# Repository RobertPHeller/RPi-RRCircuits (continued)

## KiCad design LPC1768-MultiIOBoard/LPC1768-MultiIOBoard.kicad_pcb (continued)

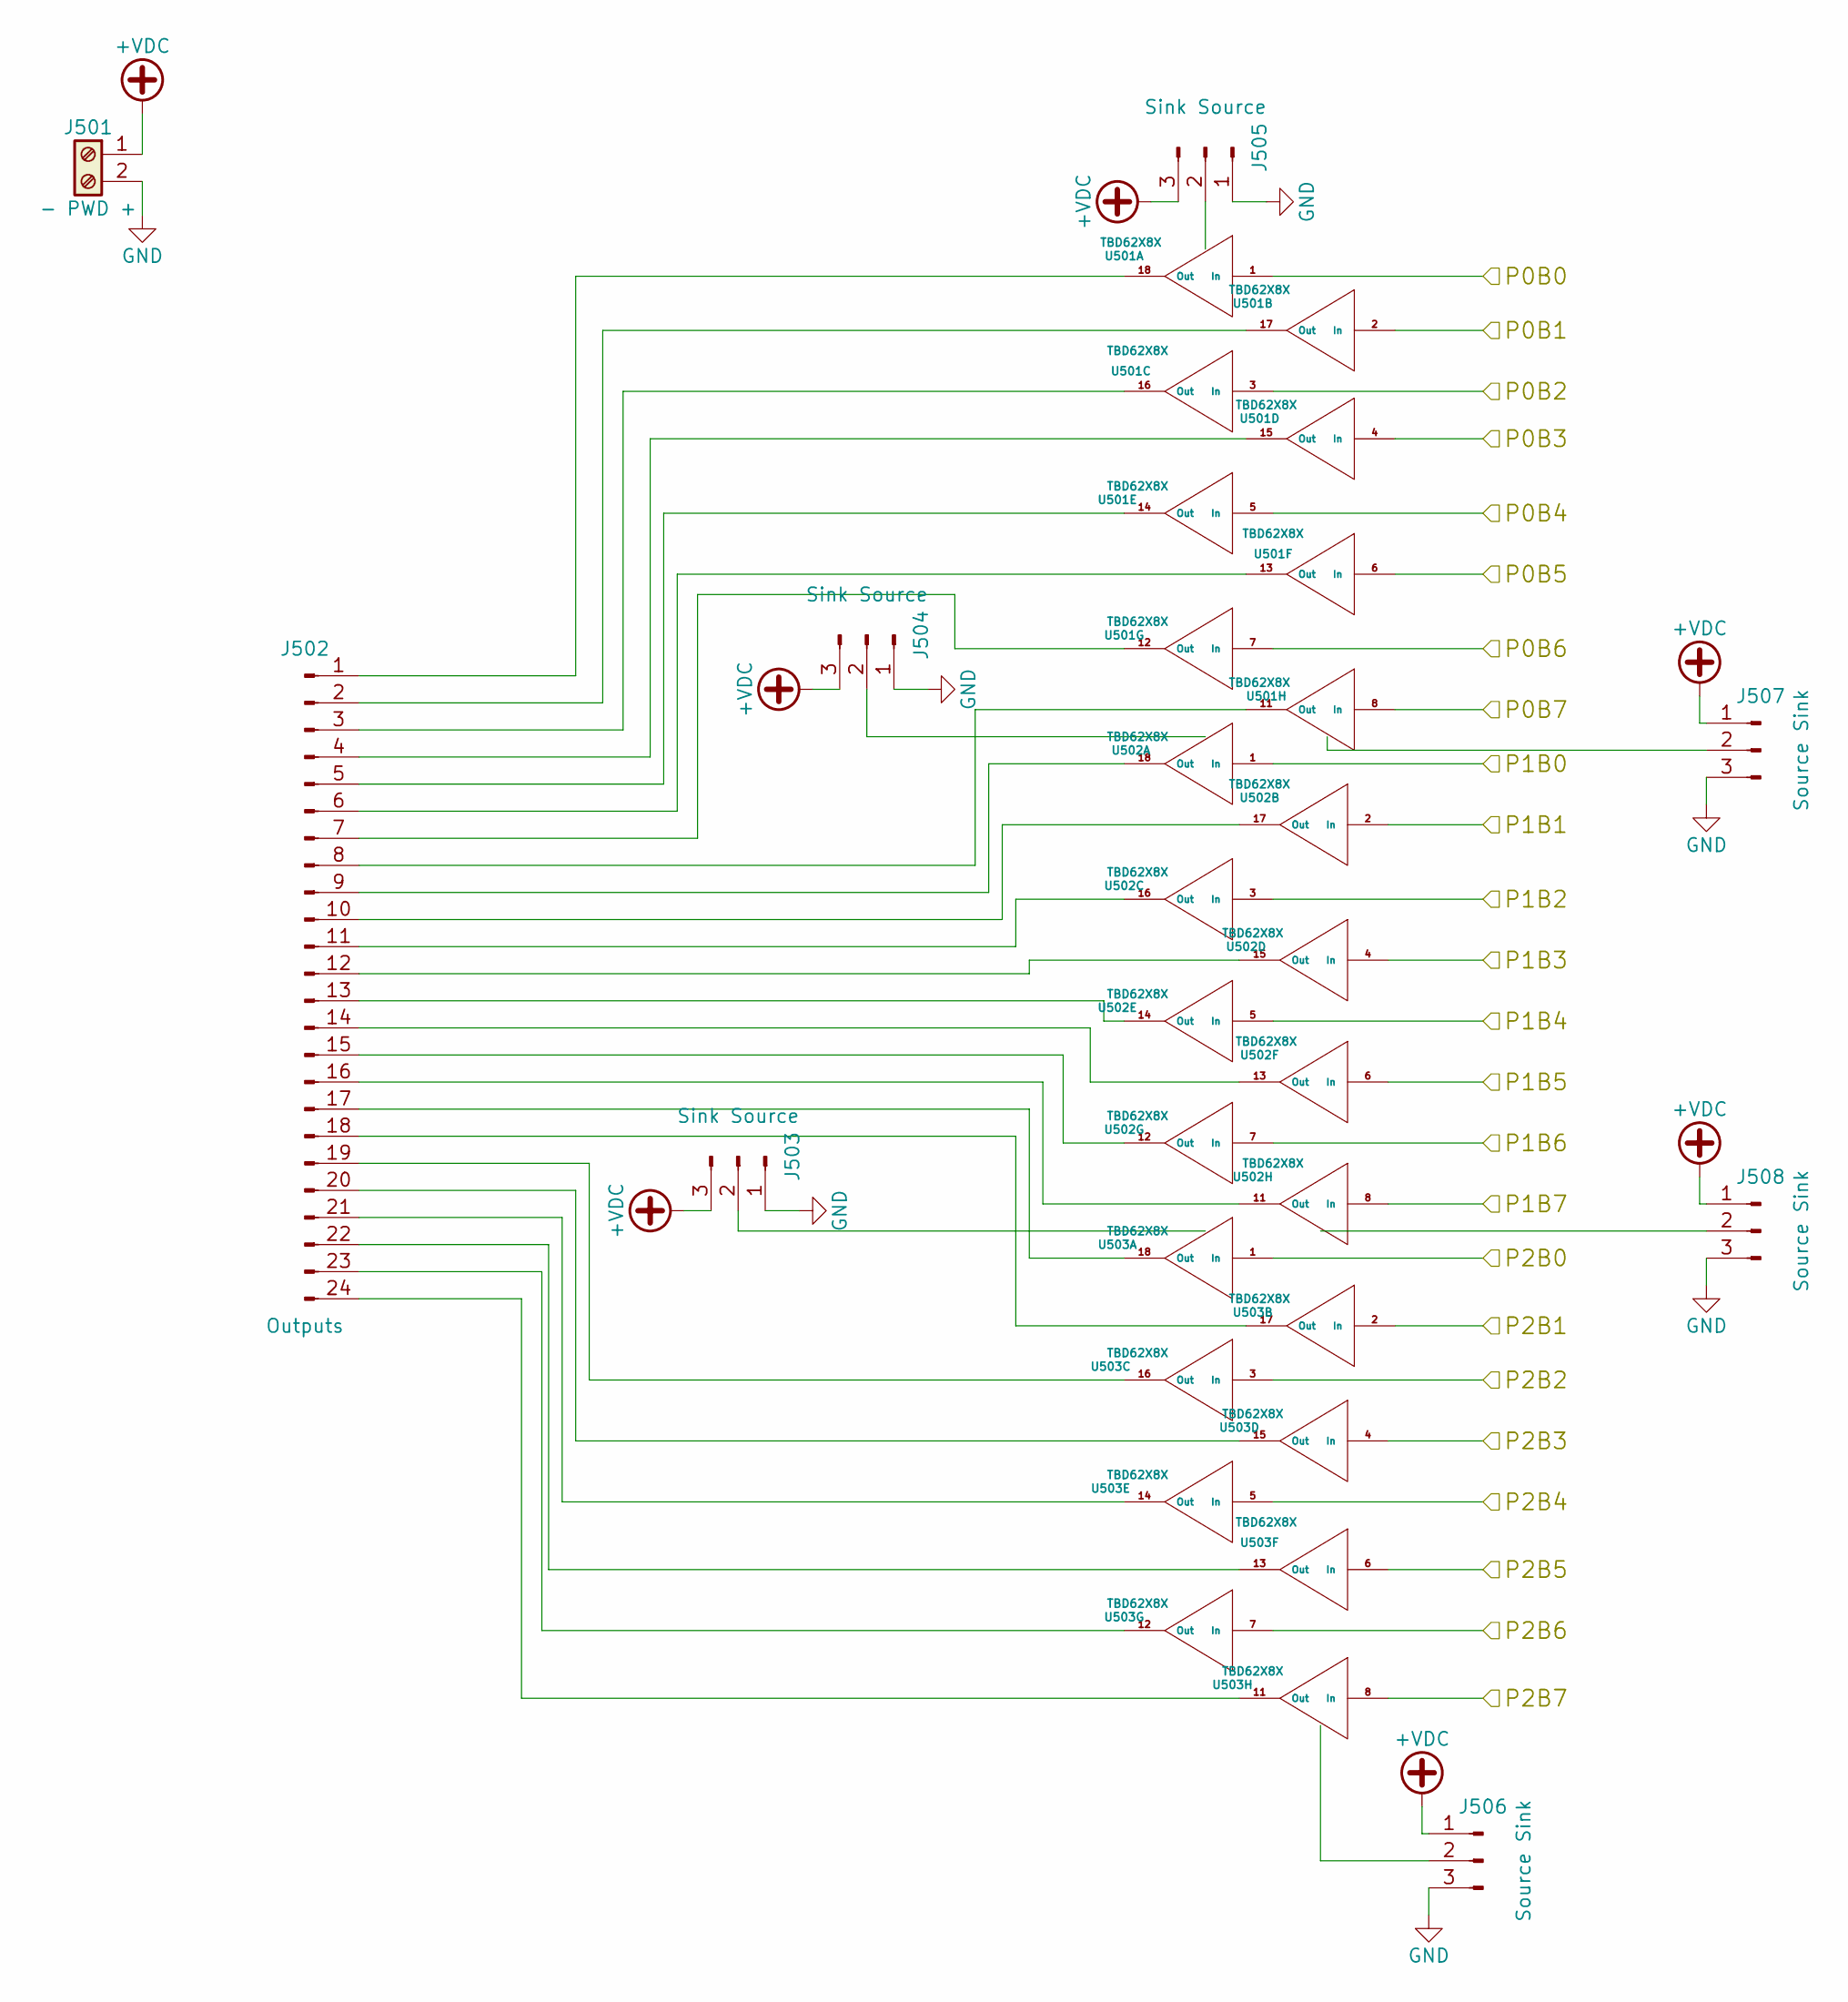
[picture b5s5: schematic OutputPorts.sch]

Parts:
J501: - PWD +; TerminalBlock_Pheonix_MPT-2.54mm_2pol
J502: Outputs; Molex_KK_396_01x24_3.96mm_RightAngle; Mouser Part Number 538-26-48-1242
J503, J504, J505: Sink Source; Pin_Header_Straight_1x03_Pitch2.54mm
J506, J507, J508: Source Sink; Pin_Header_Straight_1x03_Pitch2.54mm
U501, U502, U503: TBD62X8X; DIP-18_W7.62mm; Mouser Part Number 571-1-2199298-5

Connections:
+VDC: J501.1, J503.3, J504.3, J505.3, J506.1, J507.1, J508.1
/Micro Processor Unit/C1P0B0: U501.1 (In); also elsewhere on the board
/Micro Processor Unit/C1P0B1: U501.2 (In); also elsewhere on the board
/Micro Processor Unit/C1P0B2: U501.3 (In); also elsewhere on the board
/Micro Processor Unit/C1P0B3: U501.4 (In); also elsewhere on the board
/Micro Processor Unit/C1P0B4: U501.5 (In); also elsewhere on the board
/Micro Processor Unit/C1P0B5: U501.6 (In); also elsewhere on the board
/Micro Processor Unit/C1P0B6: U501.7 (In); also elsewhere on the board
/Micro Processor Unit/C1P0B7: U501.8 (In); also elsewhere on the board
/Micro Processor Unit/C1P1B0: U502.1 (In); also elsewhere on the board
/Micro Processor Unit/C1P1B1: U502.2 (In); also elsewhere on the board
/Micro Processor Unit/C1P1B2: U502.3 (In); also elsewhere on the board
/Micro Processor Unit/C1P1B3: U502.4 (In); also elsewhere on the board
/Micro Processor Unit/C1P1B4: U502.5 (In); also elsewhere on the board
/Micro Processor Unit/C1P1B5: U502.6 (In); also elsewhere on the board
/Micro Processor Unit/C1P1B6: U502.7 (In); also elsewhere on the board
/Micro Processor Unit/C1P1B7: U502.8 (In); also elsewhere on the board
/Micro Processor Unit/C1P2B0: U503.1 (In); also elsewhere on the board
/Micro Processor Unit/C1P2B1: U503.2 (In); also elsewhere on the board
/Micro Processor Unit/C1P2B2: U503.3 (In); also elsewhere on the board
/Micro Processor Unit/C1P2B3: U503.4 (In); also elsewhere on the board
/Micro Processor Unit/C1P2B4: U503.5 (In); also elsewhere on the board
/Micro Processor Unit/C1P2B5: U503.6 (In); also elsewhere on the board
/Micro Processor Unit/C1P2B6: U503.7 (In); also elsewhere on the board
/Micro Processor Unit/C1P2B7: U503.8 (In); also elsewhere on the board
GND: J501.2, J503.1, J504.1, J505.1, J506.3, J507.3, J508.3; also elsewhere on the board
unnamed: J502.1, U501.18 (Out)
unnamed: J502.2, U501.17 (Out)
unnamed: J502.3, U501.16 (Out)
unnamed: J502.4, U501.15 (Out)
unnamed: J502.5, U501.14 (Out)
unnamed: J502.6, U501.13 (Out)
unnamed: J502.7, U501.12 (Out)
unnamed: J502.8, U501.11 (Out)
unnamed: J502.9, U502.18 (Out)
unnamed: J502.10, U502.17 (Out)
unnamed: J502.11, U502.16 (Out)
unnamed: J502.12, U502.15 (Out)
unnamed: J502.13, U502.14 (Out)
unnamed: J502.14, U502.13 (Out)
unnamed: J502.15, U502.12 (Out)
unnamed: J502.16, U502.11 (Out)
unnamed: J502.17, U503.18 (Out)
unnamed: J502.18, U503.17 (Out)
unnamed: J502.19, U503.16 (Out)
unnamed: J502.20, U503.15 (Out)
unnamed: J502.21, U503.14 (Out)
unnamed: J502.22, U503.13 (Out)
unnamed: J502.23, U503.12 (Out)
unnamed: J502.24, U503.11 (Out)
unnamed: J503.2, U503.10 (OC)
unnamed: J504.2, U502.10 (OC)
unnamed: J505.2, U501.10 (OC)
unnamed: J506.2, U503.9 (IC)
unnamed: J507.2, U501.9 (IC)
unnamed: J508.2, U502.9 (IC)

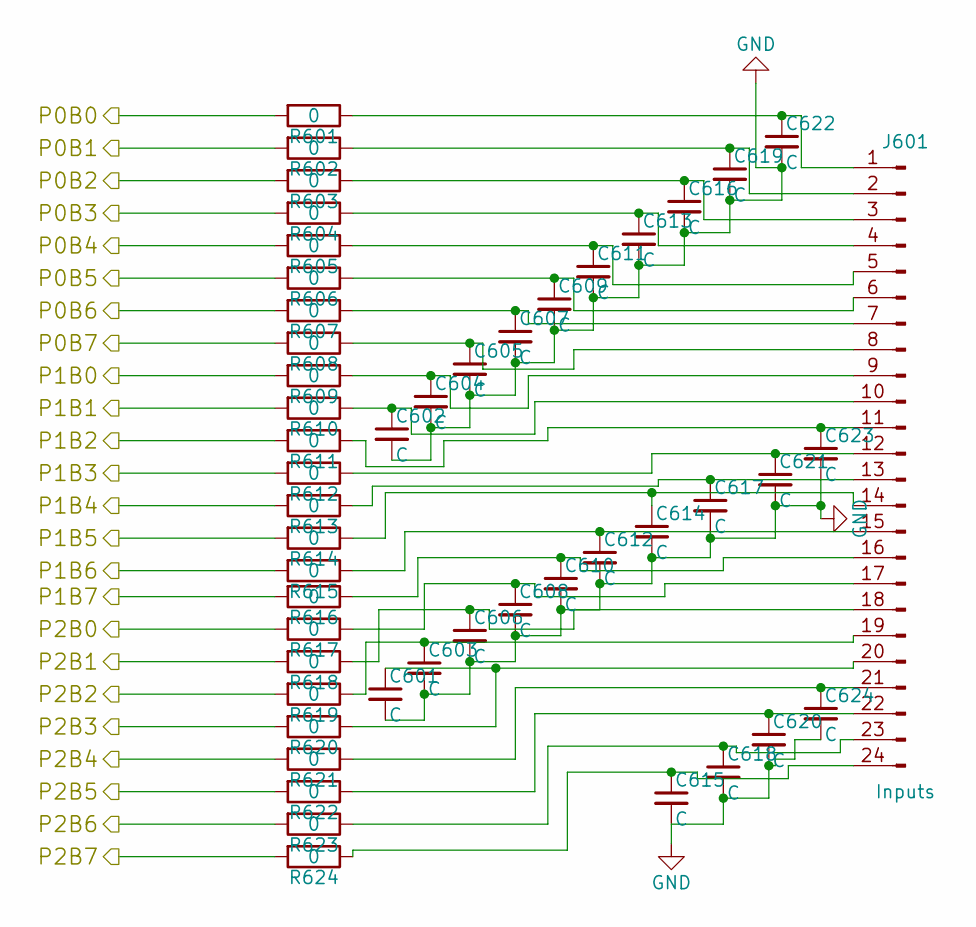
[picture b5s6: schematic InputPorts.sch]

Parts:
C601, C602, C603, C604, C605, C606, C607, C608, C609, C610, C611, C612, C613, C614, C615, C616, C617, C618, C619, C620, C621, C622, C623, C624: C; C_Disc_D3.8mm_W2.6mm_P2.50mm
J601: Inputs; Molex_KK_396_01x24_3.96mm_RightAngle; Mouser Part Number 538-26-48-1242
R601, R602, R603, R604, R605, R606, R607, R608, R609, R610, R611, R612, R613, R614, R615, R616, R617, R618, R619, R620, R621, R622, R623, R624: 0; R_Axial_DIN0207_L6.3mm_D2.5mm_P10.16mm_Horizontal_WJumper

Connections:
/Micro Processor Unit/C0P0B0: R601.2; also elsewhere on the board
/Micro Processor Unit/C0P0B1: R602.2; also elsewhere on the board
/Micro Processor Unit/C0P0B2: R603.2; also elsewhere on the board
/Micro Processor Unit/C0P0B3: R604.2; also elsewhere on the board
/Micro Processor Unit/C0P0B4: R605.2; also elsewhere on the board
/Micro Processor Unit/C0P0B5: R606.2; also elsewhere on the board
/Micro Processor Unit/C0P0B6: R607.2; also elsewhere on the board
/Micro Processor Unit/C0P0B7: R608.2; also elsewhere on the board
/Micro Processor Unit/C0P1B0: R609.2; also elsewhere on the board
/Micro Processor Unit/C0P1B1: R610.2; also elsewhere on the board
/Micro Processor Unit/C0P1B2: R611.2; also elsewhere on the board
/Micro Processor Unit/C0P1B3: R612.2; also elsewhere on the board
/Micro Processor Unit/C0P1B4: R613.2; also elsewhere on the board
/Micro Processor Unit/C0P1B5: R614.2; also elsewhere on the board
/Micro Processor Unit/C0P1B6: R615.2; also elsewhere on the board
/Micro Processor Unit/C0P1B7: R616.2; also elsewhere on the board
/Micro Processor Unit/C0P2B0: R617.2; also elsewhere on the board
/Micro Processor Unit/C0P2B1: R618.2; also elsewhere on the board
/Micro Processor Unit/C0P2B2: R619.2; also elsewhere on the board
/Micro Processor Unit/C0P2B3: R620.2; also elsewhere on the board
/Micro Processor Unit/C0P2B4: R621.2; also elsewhere on the board
/Micro Processor Unit/C0P2B5: R622.2; also elsewhere on the board
/Micro Processor Unit/C0P2B6: R623.2; also elsewhere on the board
/Micro Processor Unit/C0P2B7: R624.2; also elsewhere on the board
GND: C601.2, C602.2, C603.2, C604.2, C605.2, C606.2, C607.2, C608.2, C609.2, C610.2, C611.2, C612.2, C613.2, C614.2, C615.2, C616.2, C617.2, C618.2, C619.2, C620.2, C621.2, C622.2, C623.2, C624.2; also elsewhere on the board
unnamed: C601.1, J601.20, R620.1
unnamed: C602.1, J601.10, R610.1
unnamed: C603.1, J601.19, R619.1
unnamed: C604.1, J601.9, R609.1
unnamed: C605.1, J601.8, R608.1
unnamed: C606.1, J601.18, R618.1
unnamed: C607.1, J601.7, R607.1
unnamed: C608.1, J601.17, R617.1
unnamed: C609.1, J601.6, R606.1
unnamed: C610.1, J601.16, R616.1
unnamed: C611.1, J601.5, R605.1
unnamed: C612.1, J601.15, R615.1
unnamed: C613.1, J601.4, R604.1
unnamed: C614.1, J601.14, R614.1
unnamed: C615.1, J601.24, R624.1
unnamed: C616.1, J601.3, R603.1
unnamed: C617.1, J601.13, R613.1
unnamed: C618.1, J601.23, R623.1
unnamed: C619.1, J601.2, R602.1
unnamed: C620.1, J601.22, R622.1
unnamed: C621.1, J601.12, R612.1
unnamed: C622.1, J601.1, R601.1
unnamed: C623.1, J601.11, R611.1
unnamed: C624.1, J601.21, R621.1

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
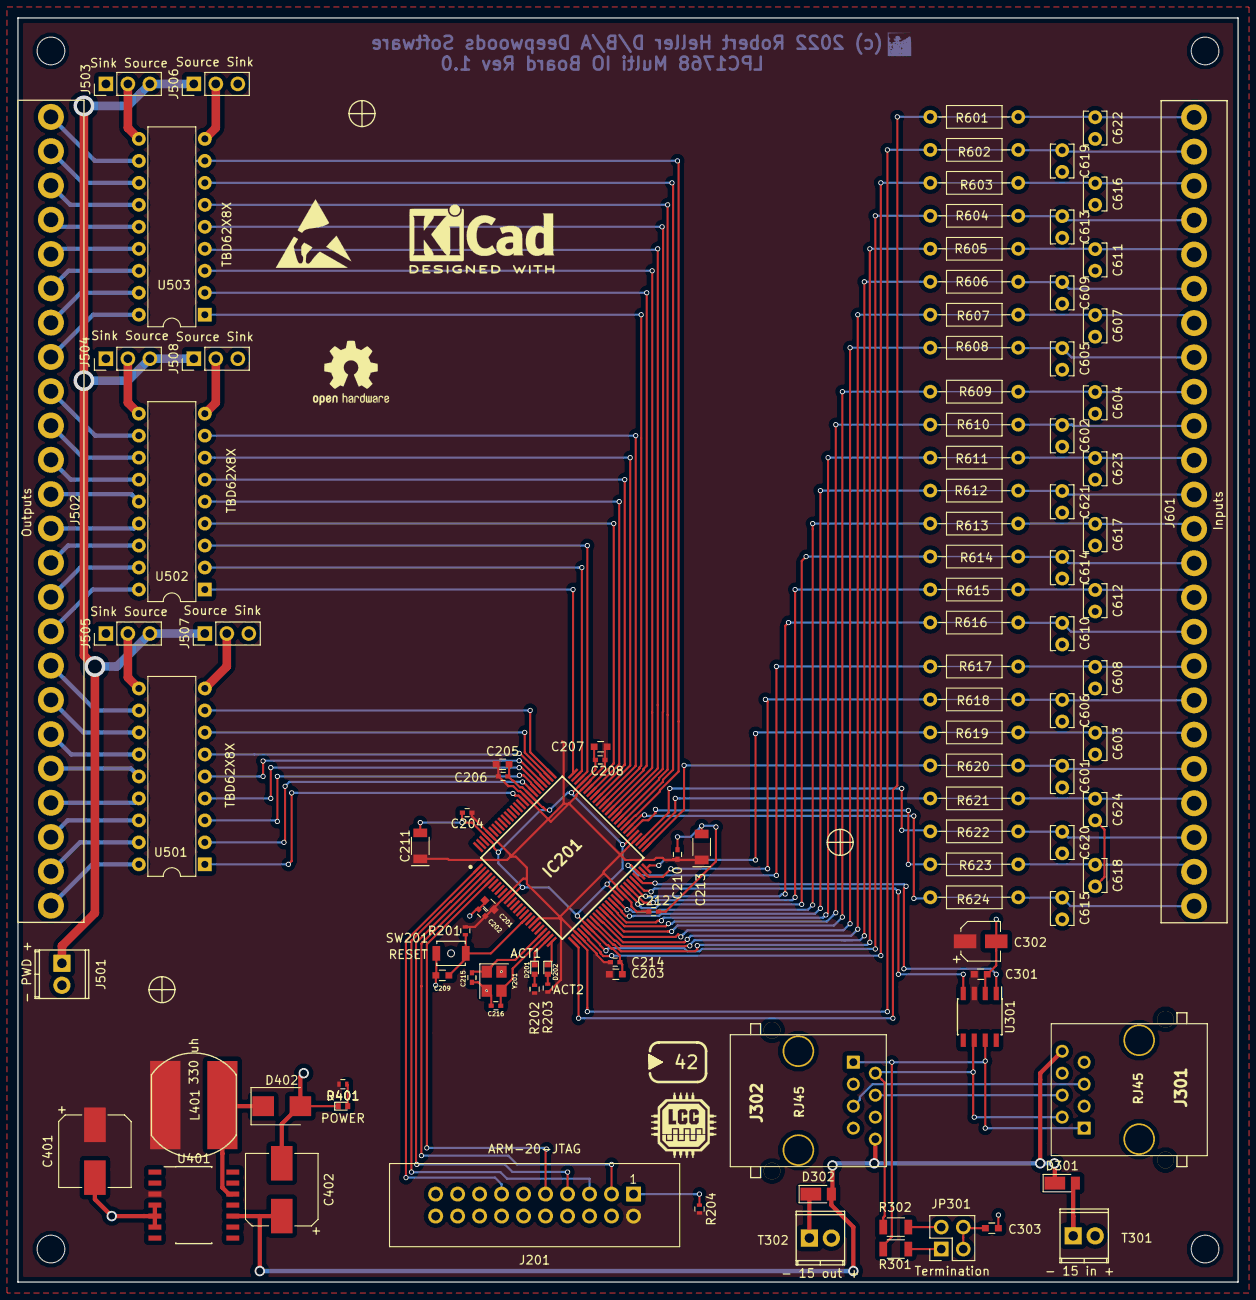
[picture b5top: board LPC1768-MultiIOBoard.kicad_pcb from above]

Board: 2 copper layers, 141.0 x 146.0 mm, 113 parts (0 on the bottom side), 132 nets.
